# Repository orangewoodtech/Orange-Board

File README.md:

# Orange-Board

Combined PCB for Arduino , ESP-32 , STM-32 ( Bluepill ) 

## Files 
1. .sch --> Schematic File 
2. .brd --> Board File 
3. .zip --> Containing Gerber files

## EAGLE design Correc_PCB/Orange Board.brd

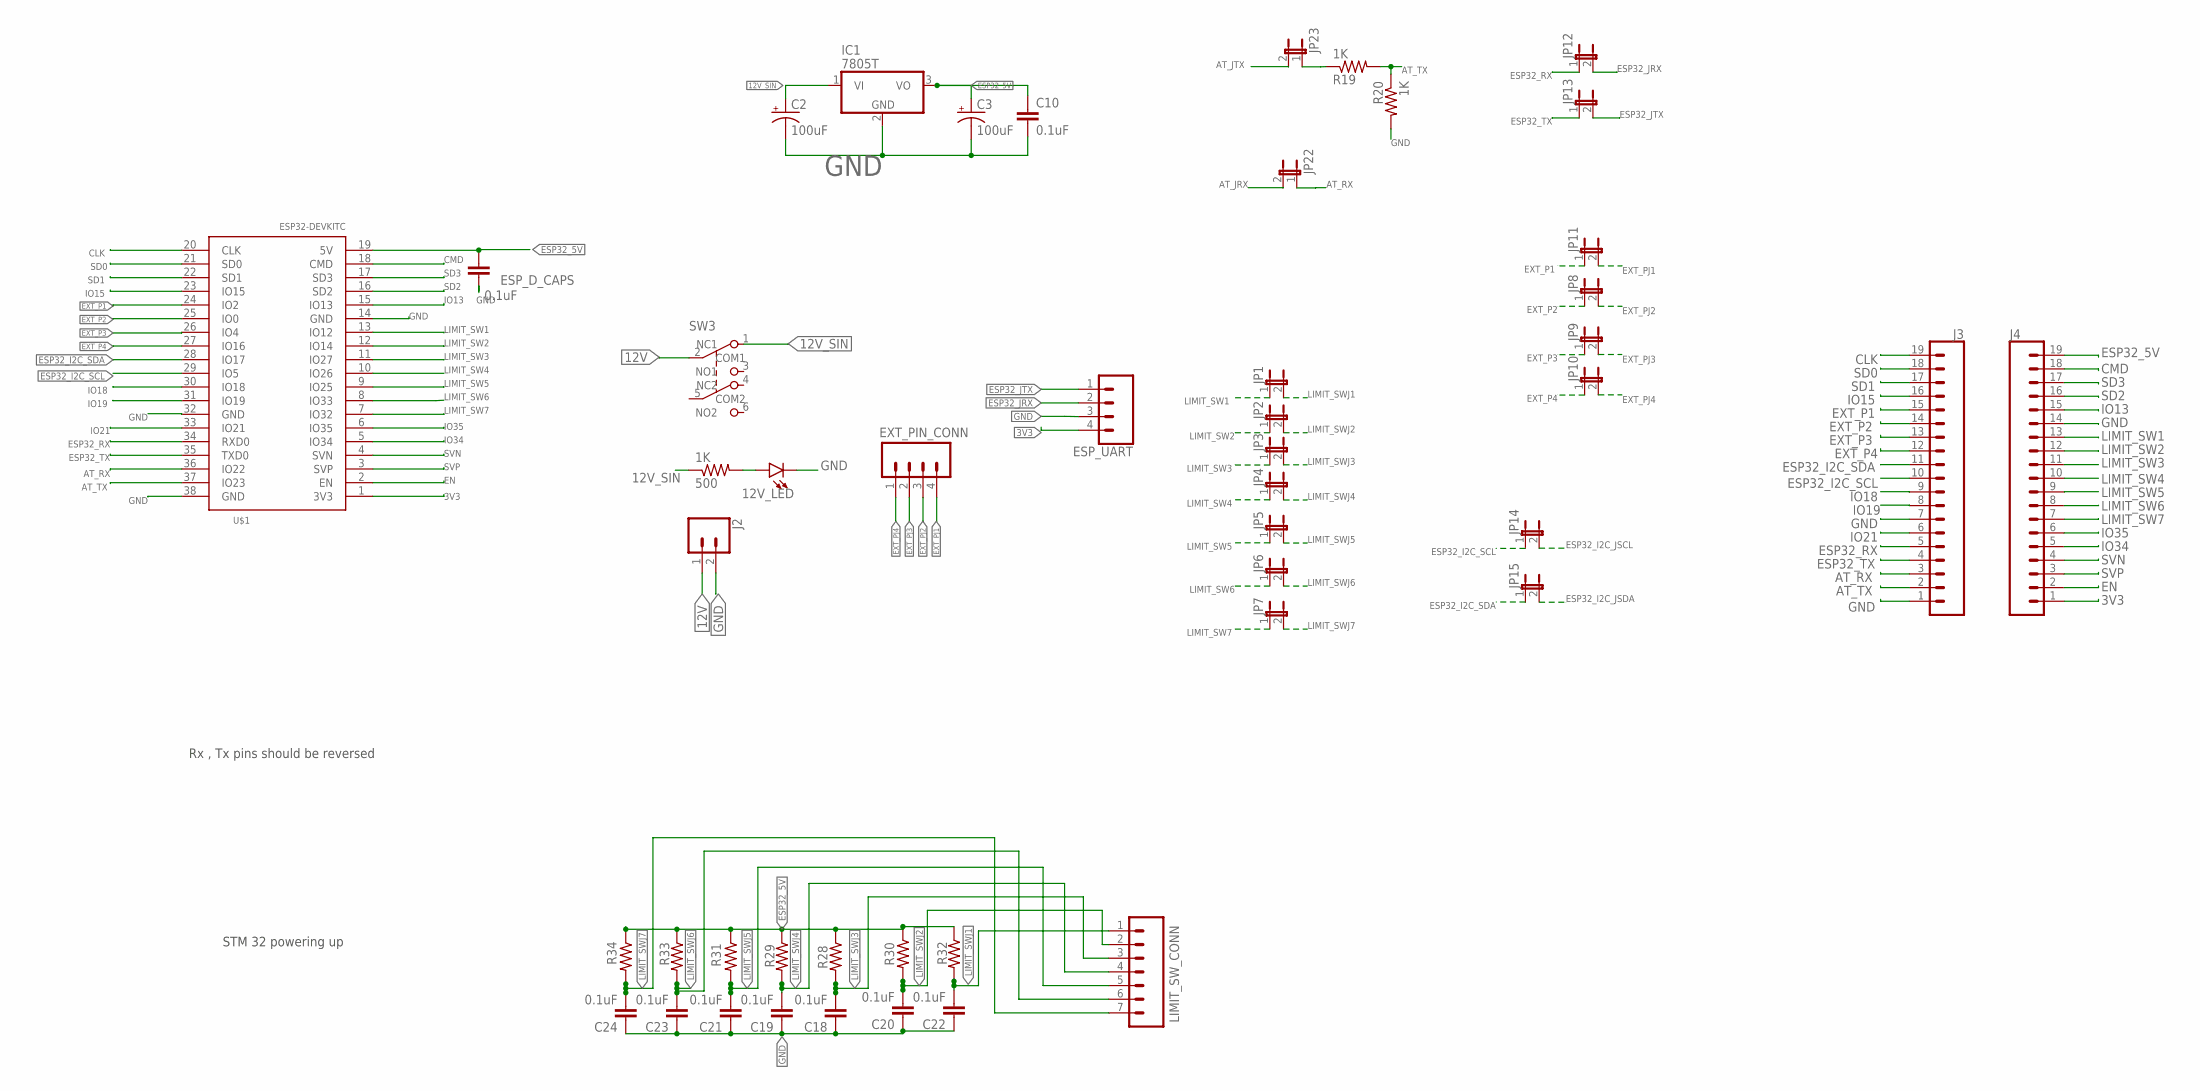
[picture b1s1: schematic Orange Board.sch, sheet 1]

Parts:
12V_LED: LED-3MM-NO_SILK; LED_3MM-NS
500: 1K; 0207/15
C2, C3: 100uF; CPOL-RADIAL-2.5MM-6.5MM
C10, C18, C19, C20, C21, C22, C23, C24: 0.1uF; CAP-PTH-SMALL-KIT
ESP_D_CAPS: 0.1uF; CAP-PTH-SMALL-KIT
ESP_UART: CONN_04; 1X04
EXT_PIN_CONN: CONN_04; 1X04
IC1: 7805T; TO220H
J2: CONN_025MM; SCREWTERMINAL-5MM-2
J3, J4: CONN_19; 1X19
JP1, JP2, JP3, JP4, JP5, JP6, JP7, JP8, JP9, JP10, JP11, JP12, JP13, JP14, JP15, JP22, JP23: JUMPER-2PTH; 1X02
LIMIT_SW_CONN: CONN_07; 1X07
R19, R20: 1K; 0207/10
R28, R29, R30, R31, R32, R33, R34: R-US_0207/10; 0207/10
SW3: SW_PUSH_DPDT; SW_PUSH_BUTTON_MINI
U$1: ESP32DEVKITC; ESP32-DEVKITC

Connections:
3V3: ESP_UART.4, J4.1, U$1.1 (3V3)
12V: J2.1, SW3.2 (COM1)
12V_SIN: 500.1, C2.1 (+), IC1.1 (VI), SW3.1 (NC1); also elsewhere on the board
AT_JRX: JP22.2; also elsewhere on the board
AT_JTX: JP23.2; also elsewhere on the board
AT_RX: J3.3, JP22.1, U$1.36 (IO22)
AT_TX: J3.2, R19.2, R20.1, U$1.37 (IO23)
CLK: J3.19, U$1.20 (CLK)
CMD: J4.18, U$1.18 (CMD)
EN: J4.2, U$1.2 (EN)
ESP32_5V: C3.1 (+), C10.1, ESP_D_CAPS.1, IC1.3 (VO), J4.19, R28.1, R29.1, R30.1, R31.1, R32.1, R33.1, R34.1, U$1.19 (5V)
ESP32_I2C_JSCL: JP14.2; also elsewhere on the board
ESP32_I2C_JSDA: JP15.2; also elsewhere on the board
ESP32_I2C_SCL: J3.10, JP14.1, U$1.29 (IO5)
ESP32_I2C_SDA: J3.11, JP15.1, U$1.28 (IO17)
ESP32_JRX: ESP_UART.2, JP12.2
ESP32_JTX: ESP_UART.1, JP13.2
ESP32_RX: J3.5, JP12.1, U$1.34 (RXD0)
ESP32_TX: J3.4, JP13.1, U$1.35 (TXD0)
EXT_P1: J3.15, JP11.1, U$1.24 (IO2)
EXT_P2: J3.14, JP8.1, U$1.25 (IO0)
EXT_P3: J3.13, JP9.1, U$1.26 (IO4)
EXT_P4: J3.12, JP10.1, U$1.27 (IO16)
EXT_PJ1: EXT_PIN_CONN.4, JP11.2
EXT_PJ2: EXT_PIN_CONN.3, JP8.2
EXT_PJ3: EXT_PIN_CONN.2, JP9.2
EXT_PJ4: EXT_PIN_CONN.1, JP10.2
GND: 12V_LED.K (C), C2.2 (-), C3.2 (-), C10.2, C18.1, C19.1, C20.1, C21.1, C22.1, C23.1, C24.1, ESP_D_CAPS.2, ESP_UART.3, IC1.2 (GND), J2.2, J3.1, J3.7, J4.14, R20.2, U$1.14 (GND), U$1.32 (GND), U$1.38 (GND); also elsewhere on the board
IO13: J4.15, U$1.15 (IO13)
IO15: J3.16, U$1.23 (IO15)
IO18: J3.9, U$1.30 (IO18)
IO19: J3.8, U$1.31 (IO19)
IO21: J3.6, U$1.33 (IO21)
IO34: J4.5, U$1.5 (IO34)
IO35: J4.6, U$1.6 (IO35)
LIMIT_SW1: J4.13, JP1.1, U$1.13 (IO12)
LIMIT_SW2: J4.12, JP2.1, U$1.12 (IO14)
LIMIT_SW3: J4.11, JP3.1, U$1.11 (IO27)
LIMIT_SW4: J4.10, JP4.1, U$1.10 (IO26)
LIMIT_SW5: J4.9, JP5.1, U$1.9 (IO25)
LIMIT_SW6: J4.8, JP6.1, U$1.8 (IO33)
LIMIT_SW7: J4.7, JP7.1, U$1.7 (IO32)
LIMIT_SWJ1: C22.2, JP1.2, LIMIT_SW_CONN.1, R32.2
LIMIT_SWJ2: C20.2, JP2.2, LIMIT_SW_CONN.2, R30.2
LIMIT_SWJ3: C18.2, JP3.2, LIMIT_SW_CONN.3, R28.2
LIMIT_SWJ4: C19.2, JP4.2, LIMIT_SW_CONN.4, R29.2
LIMIT_SWJ5: C21.2, JP5.2, LIMIT_SW_CONN.5, R31.2
LIMIT_SWJ6: C23.2, JP6.2, LIMIT_SW_CONN.6, R33.2
LIMIT_SWJ7: C24.2, JP7.2, LIMIT_SW_CONN.7, R34.2
unnamed: JP23.1, R19.1
unnamed: 12V_LED.A, 500.2
SD0: J3.18, U$1.21 (SD0)
SD1: J3.17, U$1.22 (SD1)
SD2: J4.16, U$1.16 (SD2)
SD3: J4.17, U$1.17 (SD3)
SVN: J4.4, U$1.4 (SVN)
SVP: J4.3, U$1.3 (SVP)

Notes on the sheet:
Rx , Tx pins should be reversed
STM 32 powering up

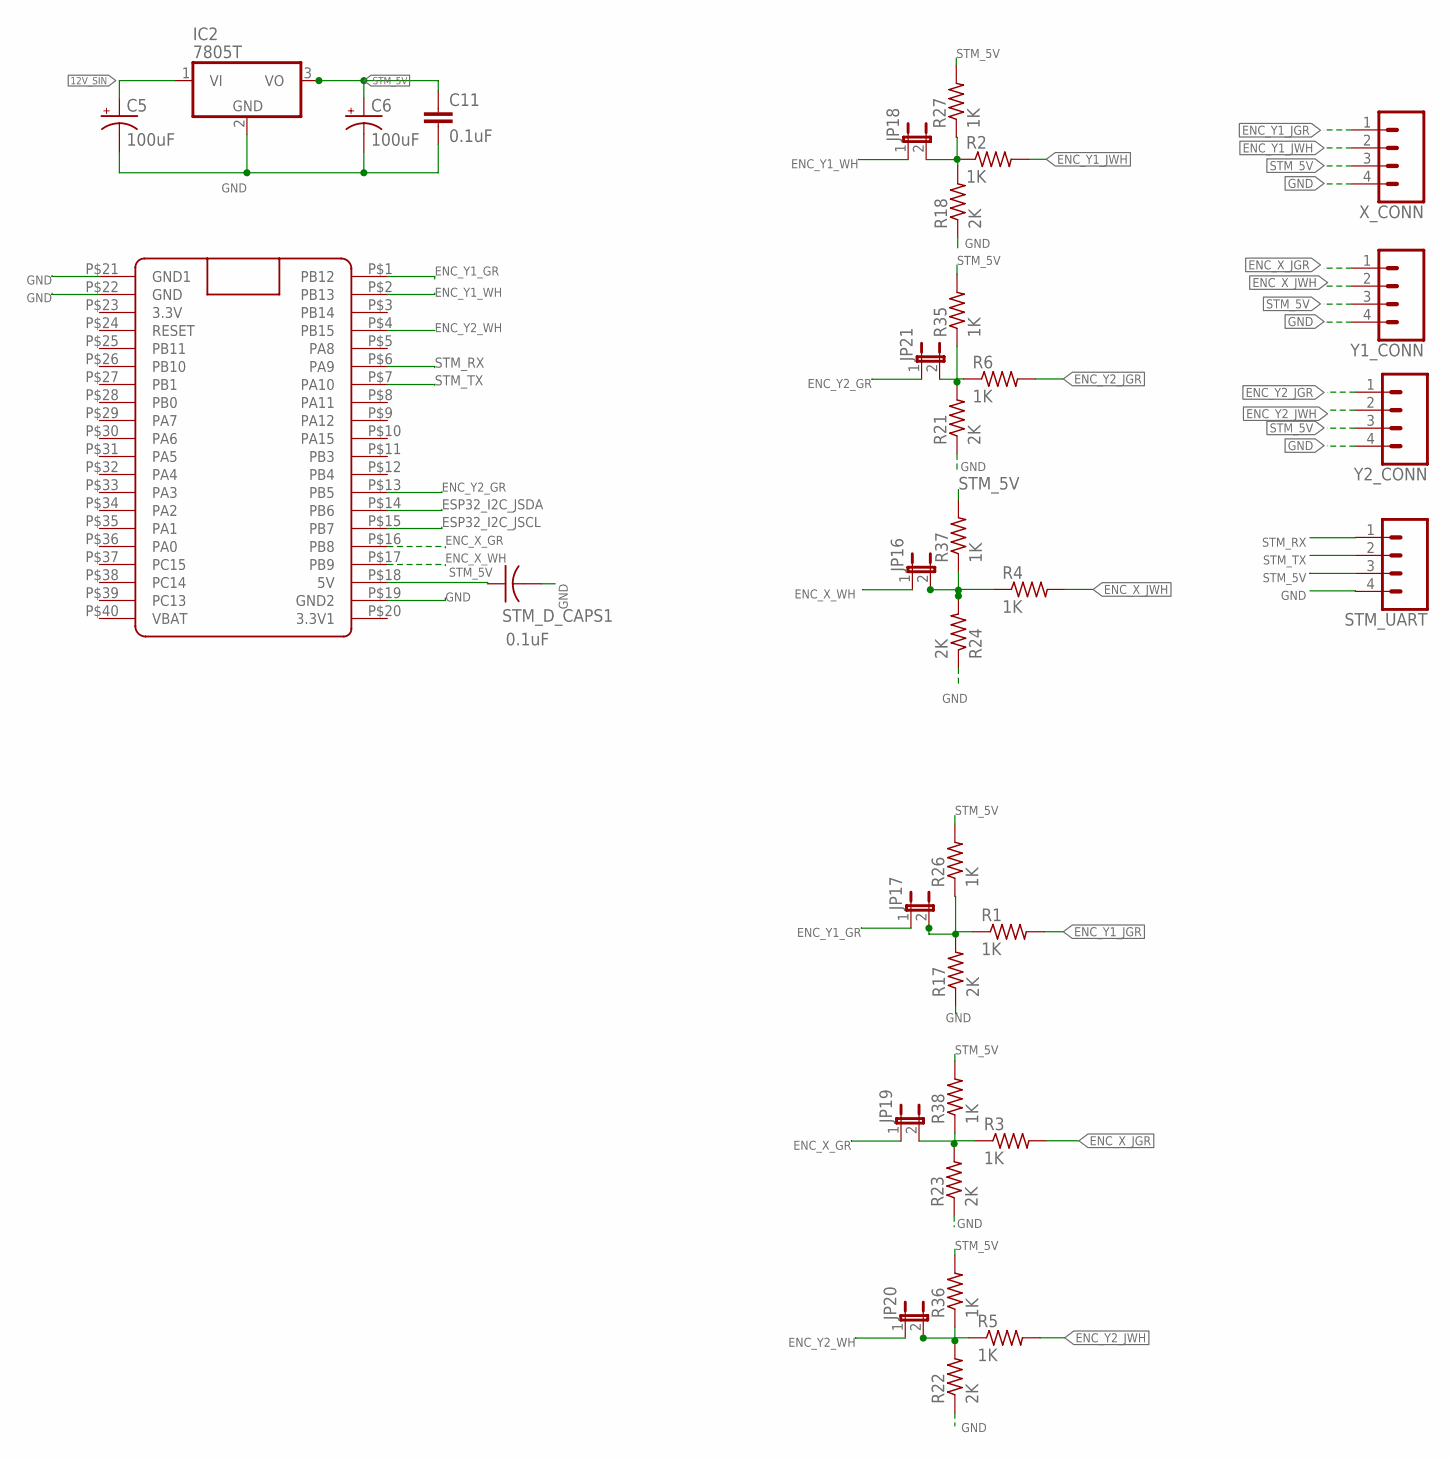
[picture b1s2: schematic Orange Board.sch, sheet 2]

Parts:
C5, C6: 100uF; CPOL-RADIAL-2.5MM-6.5MM
C11: 0.1uF; CAP-PTH-SMALL-KIT
IC2: 7805T; TO220H
JP16, JP17, JP18, JP19, JP20, JP21: JUMPER-2PTH; 1X02
R1, R2, R3, R4, R5, R6, R26, R27, R35, R36, R37, R38: 1K; 0207/10
R17, R18, R21, R22, R23, R24: 2K; 0207/10
STM_D_CAPS1: 0.1uF; C025-024X044
STM_UART: CONN_04; 1X04
U$2: BLUE_PILLADVANCED; BLUE_PILL_ADV
X_CONN: CONN_04; 1X04
Y1_CONN, Y2_CONN: CONN_04; 1X04

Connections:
12V_SIN: C5.1 (+), IC2.1 (VI); also elsewhere on the board
ENC_X_GR: JP19.1, U$2.P$16 (PB8)
ENC_X_JGR: R3.2, Y1_CONN.1
ENC_X_JWH: R4.2, Y1_CONN.2
ENC_X_WH: JP16.1, U$2.P$17 (PB9)
ENC_Y1_GR: JP17.1, U$2.P$1 (PB12)
ENC_Y1_JGR: R1.2, X_CONN.1
ENC_Y1_JWH: R2.2, X_CONN.2
ENC_Y1_WH: JP18.1, U$2.P$2 (PB13)
ENC_Y2_GR: JP21.1, U$2.P$13 (PB5)
ENC_Y2_JGR: R6.2, Y2_CONN.1
ENC_Y2_JWH: R5.2, Y2_CONN.2
ENC_Y2_WH: JP20.1, U$2.P$4 (PB15)
ESP32_I2C_JSCL: U$2.P$15 (PB7); also elsewhere on the board
ESP32_I2C_JSDA: U$2.P$14 (PB6); also elsewhere on the board
GND: C5.2 (-), C6.2 (-), C11.2, IC2.2 (GND), R17.1, R18.1, R21.1, R22.1, R23.1, R24.1, STM_D_CAPS1.2, STM_UART.4, U$2.P$19 (GND2), U$2.P$21 (GND1), U$2.P$22 (GND), X_CONN.4, Y1_CONN.4, Y2_CONN.4; also elsewhere on the board
unnamed: JP17.2, R1.1, R17.2, R26.1
unnamed: JP19.2, R3.1, R23.2, R38.1
unnamed: JP16.2, R4.1, R24.2, R37.1
unnamed: JP18.2, R2.1, R18.2, R27.1
unnamed: JP21.2, R6.1, R21.2, R35.1
unnamed: JP20.2, R5.1, R22.2, R36.1
STM_5V: C6.1 (+), C11.1, IC2.3 (VO), R26.2, R27.2, R35.2, R36.2, R37.2, R38.2, STM_D_CAPS1.1, STM_UART.3, U$2.P$18 (5V), X_CONN.3, Y1_CONN.3, Y2_CONN.3
STM_RX: STM_UART.1, U$2.P$6 (PA9)
STM_TX: STM_UART.2, U$2.P$7 (PA10)

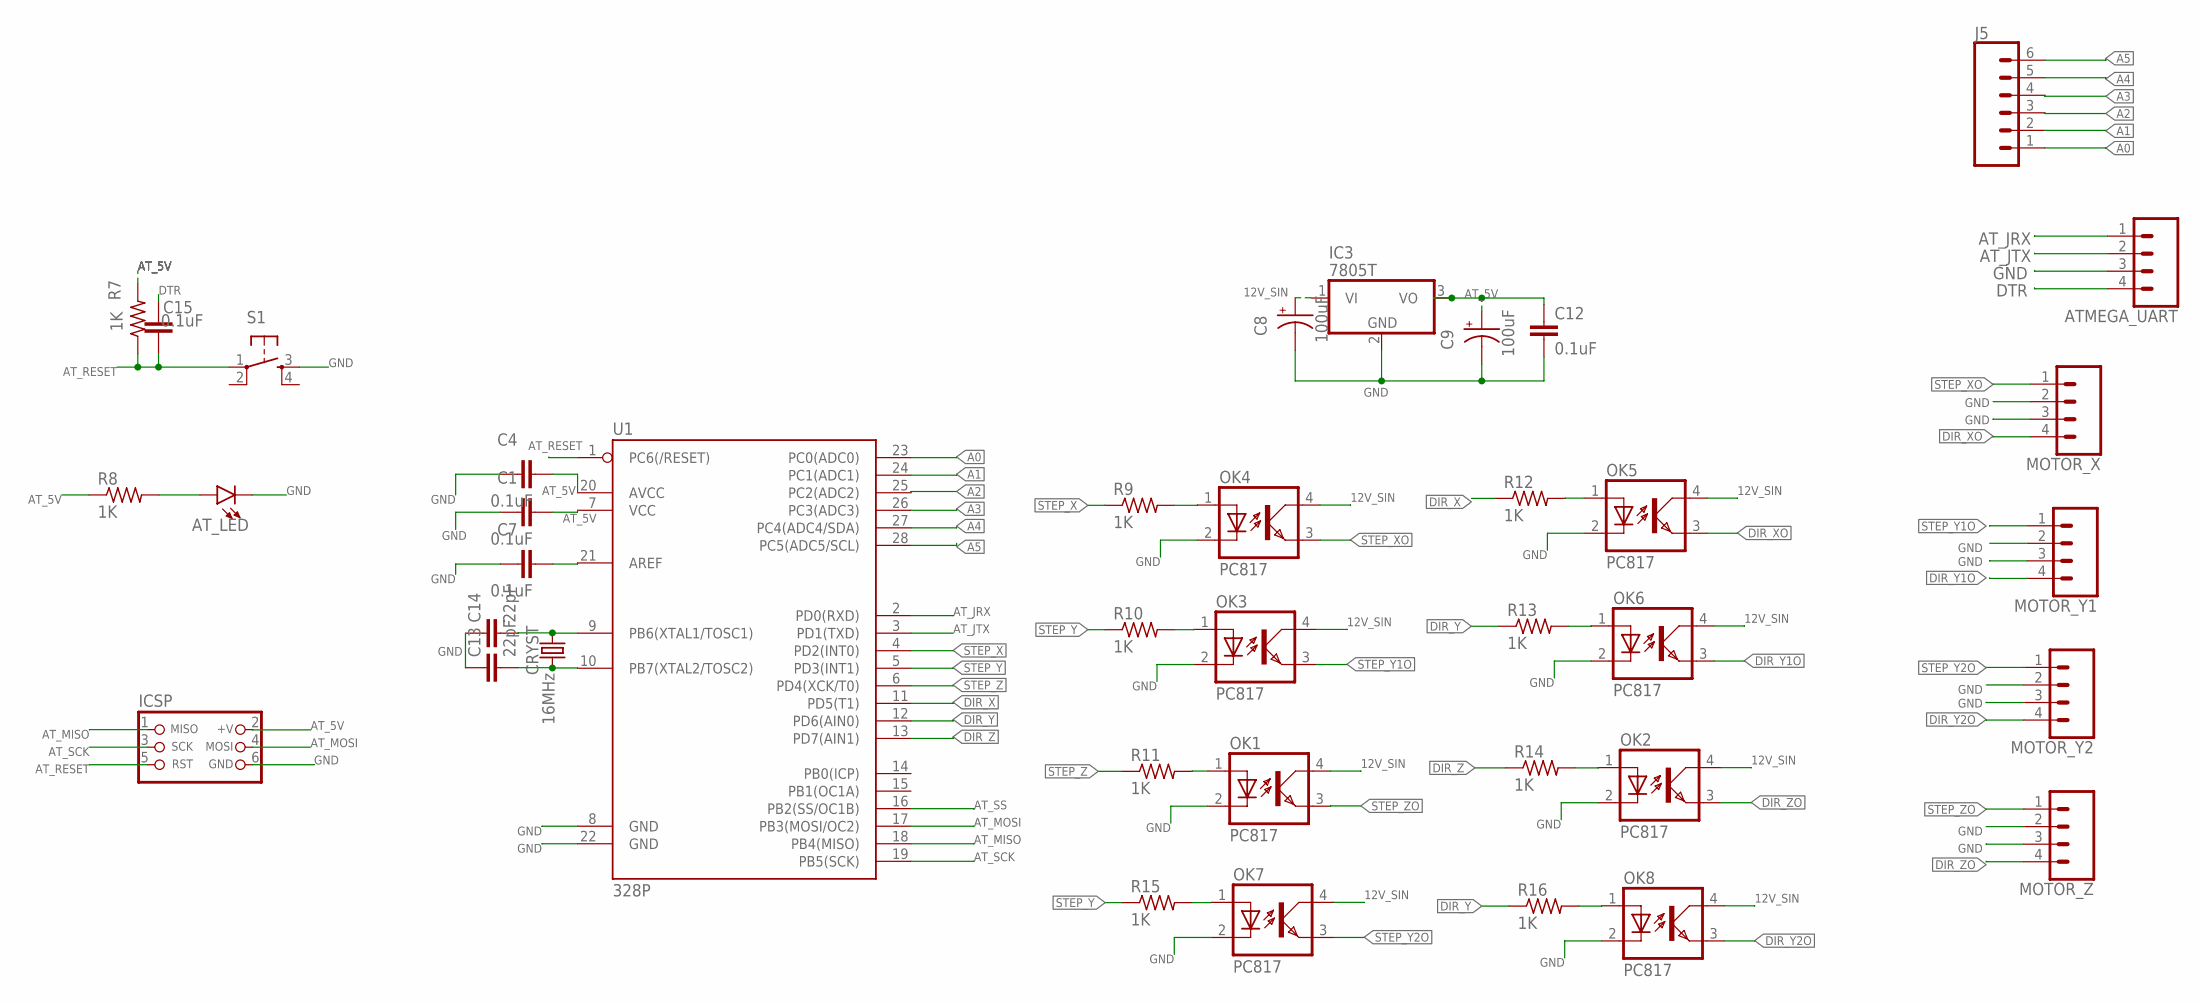
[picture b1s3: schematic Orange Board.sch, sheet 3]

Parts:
ATMEGA_UART: CONN_04; 1X04
AT_LED: LED-3MM-NO_SILK; LED_3MM-NS
C1, C4, C7, C12, C15: 0.1uF; CAP-PTH-SMALL-KIT
C8, C9: 100uF; CPOL-RADIAL-2.5MM-6.5MM
C13, C14: 22pF; CAP-PTH-2.54
CRYST: 16MHz; HC49US
IC3: 7805T; TO220H
ICSP: CON_HEADER_PRG_AVR_ICSP-PTH; HEADER_PRG_2X03
J5: CONN_06NO_SILK_FEMALE_PTH; 1X06_NO_SILK
MOTOR_X: CONN_04; 1X04
MOTOR_Y1, MOTOR_Y2: CONN_04; 1X04
MOTOR_Z: CONN_04; 1X04
OK1, OK2, OK3, OK4, OK5, OK6, OK7, OK8: PC817; DIL04
R7, R8, R9, R10, R11, R12, R13, R14, R15, R16: 1K; 0207/10
S1: TAC_SWITCHPTH; TACTILE-PTH
U1: 328P; DIP28

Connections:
12V_SIN: C8.1 (+), IC3.1 (VI), OK1.4 (COL), OK2.4 (COL), OK3.4 (COL), OK4.4 (COL), OK5.4 (COL), OK6.4 (COL), OK7.4 (COL), OK8.4 (COL); also elsewhere on the board
A0: J5.1, U1.23 (PC0(ADC0))
A1: J5.2, U1.24 (PC1(ADC1))
A2: J5.3, U1.25 (PC2(ADC2))
A3: J5.4, U1.26 (PC3(ADC3))
A4: J5.5, U1.27 (PC4(ADC4/SDA))
A5: J5.6, U1.28 (PC5(ADC5/SCL))
AT_5V: C1.1, C4.1, C9.1 (+), C12.1, IC3.3 (VO), ICSP.2 (+V), R7.2, R8.1, U1.7 (VCC), U1.20 (AVCC)
AT_JRX: ATMEGA_UART.1, U1.2 (PD0(RXD)); also elsewhere on the board
AT_JTX: ATMEGA_UART.2, U1.3 (PD1(TXD)); also elsewhere on the board
AT_MISO: ICSP.1 (MISO), U1.18 (PB4(MISO))
AT_MOSI: ICSP.4 (MOSI), U1.17 (PB3(MOSI/OC2))
AT_RESET: C15.1, ICSP.5 (RST), R7.1, S1.1, U1.1 (PC6(/RESET))
AT_SCK: ICSP.3 (SCK), U1.19 (PB5(SCK))
AT_SS: U1.16 (PB2(SS/OC1B))
DIR_X: R12.1, U1.11 (PD5(T1))
DIR_XO: MOTOR_X.4, OK5.3 (EMIT)
DIR_Y: R13.1, R16.1, U1.12 (PD6(AIN0))
DIR_Y1O: MOTOR_Y1.4, OK6.3 (EMIT)
DIR_Y2O: MOTOR_Y2.4, OK8.3 (EMIT)
DIR_Z: R14.1, U1.13 (PD7(AIN1))
DIR_ZO: MOTOR_Z.4, OK2.3 (EMIT)
DTR: ATMEGA_UART.4, C15.2
GND: ATMEGA_UART.3, AT_LED.K (C), C1.2, C4.2, C7.2, C8.2 (-), C9.2 (-), C12.2, C13.1, C14.1, IC3.2 (GND), ICSP.6 (GND), MOTOR_X.2, MOTOR_X.3, MOTOR_Y1.2, MOTOR_Y1.3, MOTOR_Y2.2, MOTOR_Y2.3, MOTOR_Z.2, MOTOR_Z.3, OK1.2 (C), OK2.2 (C), OK3.2 (C), OK4.2 (C), OK5.2 (C), OK6.2 (C), OK7.2 (C), OK8.2 (C), S1.3, U1.8 (GND), U1.22 (GND); also elsewhere on the board
unnamed: C13.2, CRYST.1, U1.10 (PB7(XTAL2/TOSC2))
unnamed: C14.2, CRYST.2, U1.9 (PB6(XTAL1/TOSC1))
unnamed: AT_LED.A, R8.2
unnamed: C7.1, U1.21 (AREF)
unnamed: OK4.1 (A), R9.2
unnamed: OK3.1 (A), R10.2
unnamed: OK1.1 (A), R11.2
unnamed: OK5.1 (A), R12.2
unnamed: OK2.1 (A), R14.2
unnamed: OK6.1 (A), R13.2
unnamed: OK7.1 (A), R15.2
unnamed: OK8.1 (A), R16.2
STEP_X: R9.1, U1.4 (PD2(INT0))
STEP_XO: MOTOR_X.1, OK4.3 (EMIT)
STEP_Y: R10.1, R15.1, U1.5 (PD3(INT1))
STEP_Y1O: MOTOR_Y1.1, OK3.3 (EMIT)
STEP_Y2O: MOTOR_Y2.1, OK7.3 (EMIT)
STEP_Z: R11.1, U1.6 (PD4(XCK/T0))
STEP_ZO: MOTOR_Z.1, OK1.3 (EMIT)

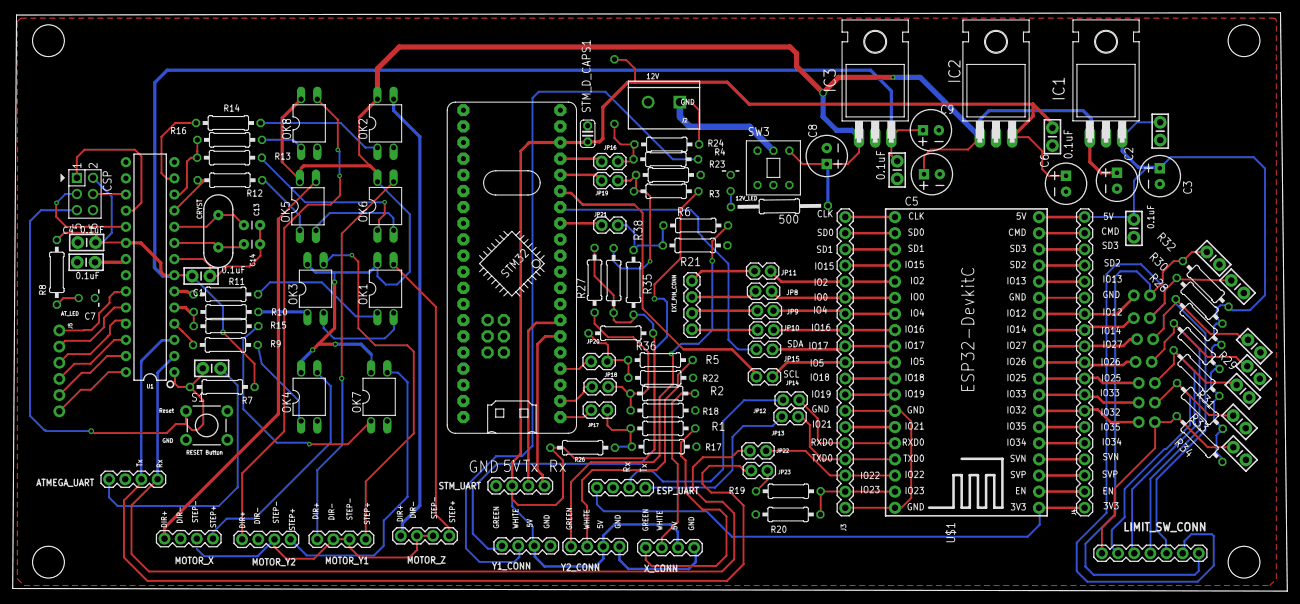
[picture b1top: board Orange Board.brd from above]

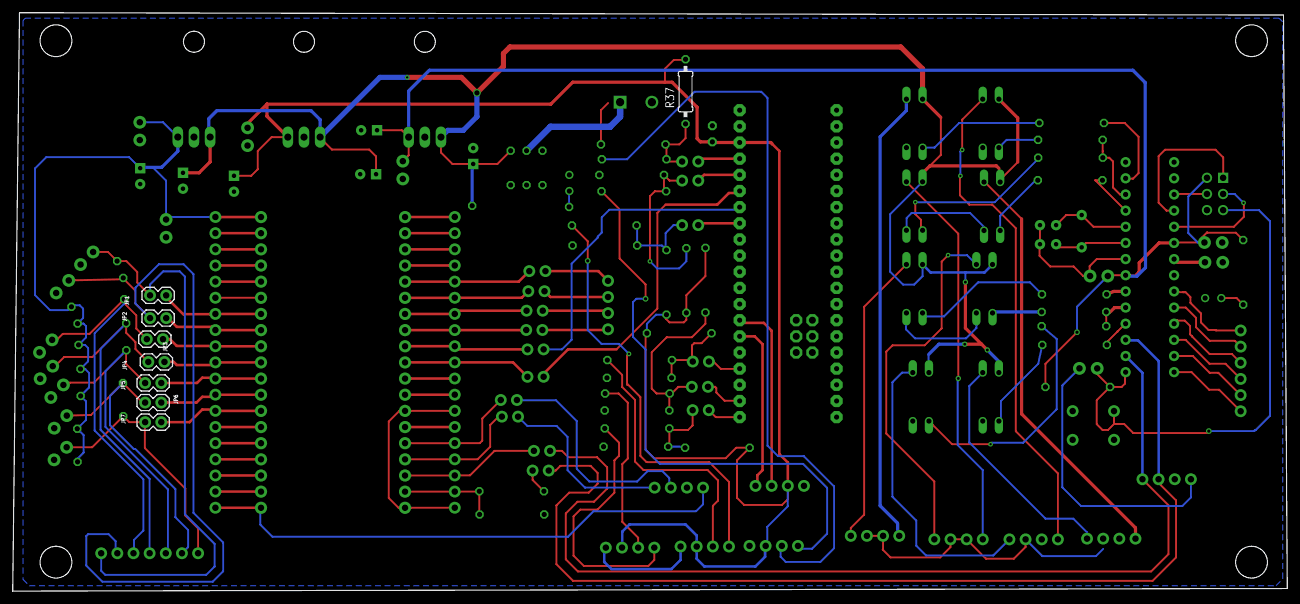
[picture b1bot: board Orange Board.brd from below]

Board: 2 copper layers, 200.4 x 90.9 mm, 121 parts (8 on the bottom side), 116 nets.

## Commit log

2018-06-11 Orange Board PCB
2018-06-12 Readme File Added
2018-06-12 Readme File Updated
2018-06-21 Corrected PCB added

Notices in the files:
parts and their libraries:
SparkFun-LED: Licensing: Creative Commons ShareAlike 4.0 International - https://creativecommons.org/licenses/by-sa/4.0
